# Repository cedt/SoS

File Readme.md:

# Science on a Stick 

---

### Folder Structure 
```
.
├── Arduino Code 				→ Contains code to be uploaded to Arduino 
│   └── SOS_Arduino_code
│       └── SOS_Arduino_code.ino
├── Arduino PCB and Hardware			→ Contains Schematic, BOM etc
│   ├── BOM-magnetic_switch_sos_v1-2022.pdf	→ Bill of Materials for Reed switch circuit
│   ├── BOM-ScienceonStick_V7-April2022.pdf	→ Bill of Materials for Main PCB
│   ├── Hardware_Acquisition_Sources.docx	→ Suggested sources to acquire components
│   ├── magnetic_switch_sos_v1-2022.sch 	→ Circuit for trigger switch
│   ├── photogate-sos-v2-2022.brd
│   ├── photogate-sos-v2-2022.sch
│   ├── ScienceOnStick_V7-April2022.brd
│   └── ScienceOnStick_V7-April2022.sch 	→ Circuit for main PCB
├── Images and Photographs
│   └── plots
│       └── ... plots created using experiments ... 
├── Python Code
│   ├── Analysis.ipynb
│   └── SoS_Acquisition.py
└── Structure
    ├── Structure Type 1
    │   ├── bar_inside.sbp
    │   ├── bar_outside.sbp
    │   ├── bars.crv
    │   ├── bars.png
    │   ├── base.crv
    │   ├── base_outside.sbp
    │   ├── base.png
    │   ├── flange.crv
    │   ├── flange_inner.sbp
    │   ├── flange_outside.sbp
    │   ├── flange.png
    │   ├── inside.sbp
    │   ├── via.crv
    │   ├── via_inside.sbp
    │   ├── via_outside.sbp
    │   └── via.png
    └── Structure Type 2
        ├── base.crv
        ├── base.png
        ├── correction.sbp
        ├── inside_baseandvia.sbp
        ├── outer_baseandvia.sbp
        ├── stand.crv
        ├── stand_in.sbp
        ├── stand_out.sbp
        ├── stand.png
        ├── via.crv
        ├── VIA-INNER.LOG
        ├── via-inner.sbp
        ├── VIA_OUTER.LOG
        ├── via_outer.sbp
        └── via.png
 ```

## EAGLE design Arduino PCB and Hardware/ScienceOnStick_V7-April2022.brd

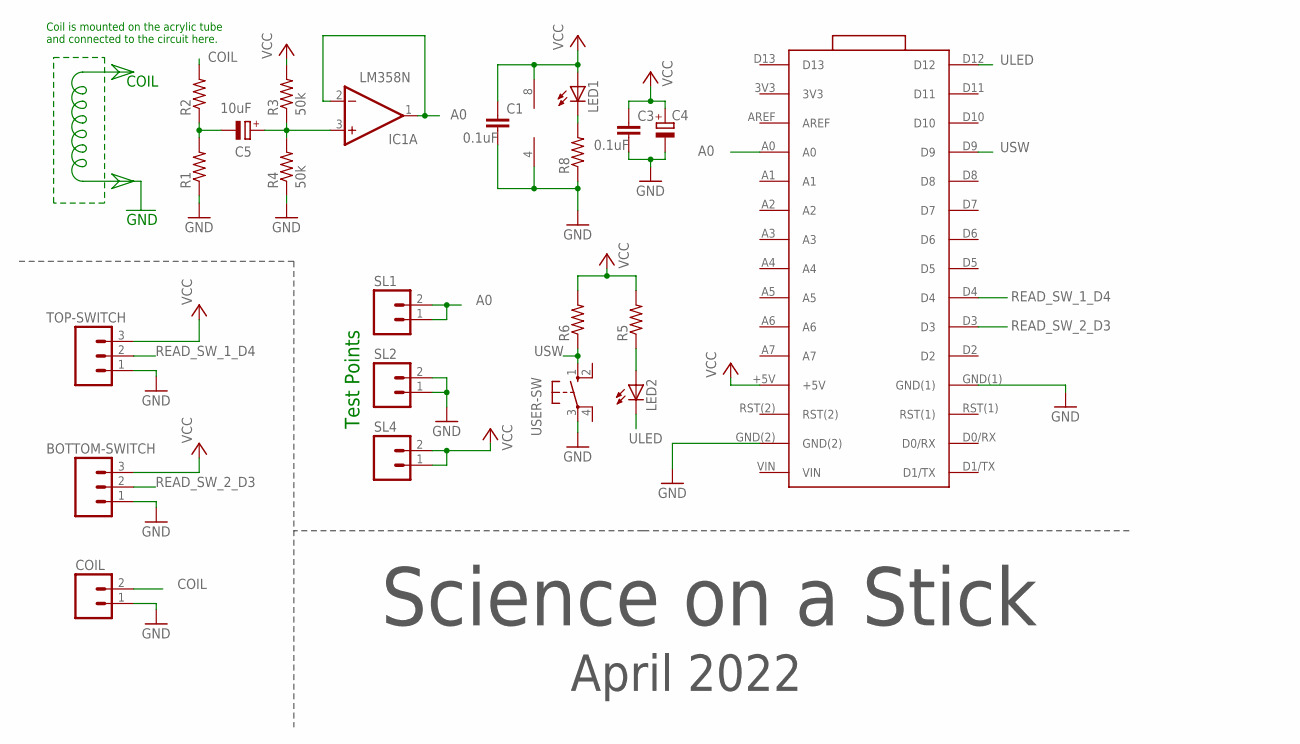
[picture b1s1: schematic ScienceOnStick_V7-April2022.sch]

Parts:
BOTTOM-SWITCH: M03; 03P
C1, C3: 0.1uF; C025-025X050
C4: CPOL-EUE2.5-6; E2,5-6
C5: 10uF; E2,5-6
COIL: M02; 02P
IC1: LM358N; DIL08
LED1, LED2: LED3MM
R1, R2, R5, R6, R8: RESISTOR0207/7; 0207/7
R3, R4: 50k; 0207/7
SL1, SL2, SL4: M02; 02P
TOP-SWITCH: M03; 03P
U$1: ARDUINO_NANO_3_ARDUINO(NANO_3.0); ARDUINO_NANO_3_ARDUINO_NANO_30PIN
USER-SW: 40-XX; B3F-40XX

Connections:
A0: IC1.1 (OUT), IC1.2 (-IN), SL1.1, SL1.2, U$1.A0
CLAMP_SIGNAL: C5.+, IC1.3 (+IN), R3.1, R4.2
COIL: COIL.2, R2.2
GND: BOTTOM-SWITCH.1, C1.2, C3.2, C4.-, COIL.1, IC1.4 (V-), R1.1, R4.1, R8.1, SL2.1, SL2.2, TOP-SWITCH.1, U$1.GND(1), U$1.GND(2), USER-SW.3
unnamed: C5.-, R1.2, R2.1
unnamed: LED2.A, R5.1
unnamed: LED1.K (C), R8.2
READ_SW_1_D4: TOP-SWITCH.2, U$1.D4
READ_SW_2_D3: BOTTOM-SWITCH.2, U$1.D3
ULED: LED2.K (C), U$1.D12
USW: R6.1, U$1.D9, USER-SW.1 (S)
VCC: BOTTOM-SWITCH.3, C1.1, C3.1, C4.+, IC1.8 (V+), LED1.A, R3.2, R5.2, R6.2, SL4.1, SL4.2, TOP-SWITCH.3, U$1.+5V

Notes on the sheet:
Science on a Stick
April 2022
Coil is mounted on the acrylic tube and connected to the circuit here.
COIL
GND
Test Points

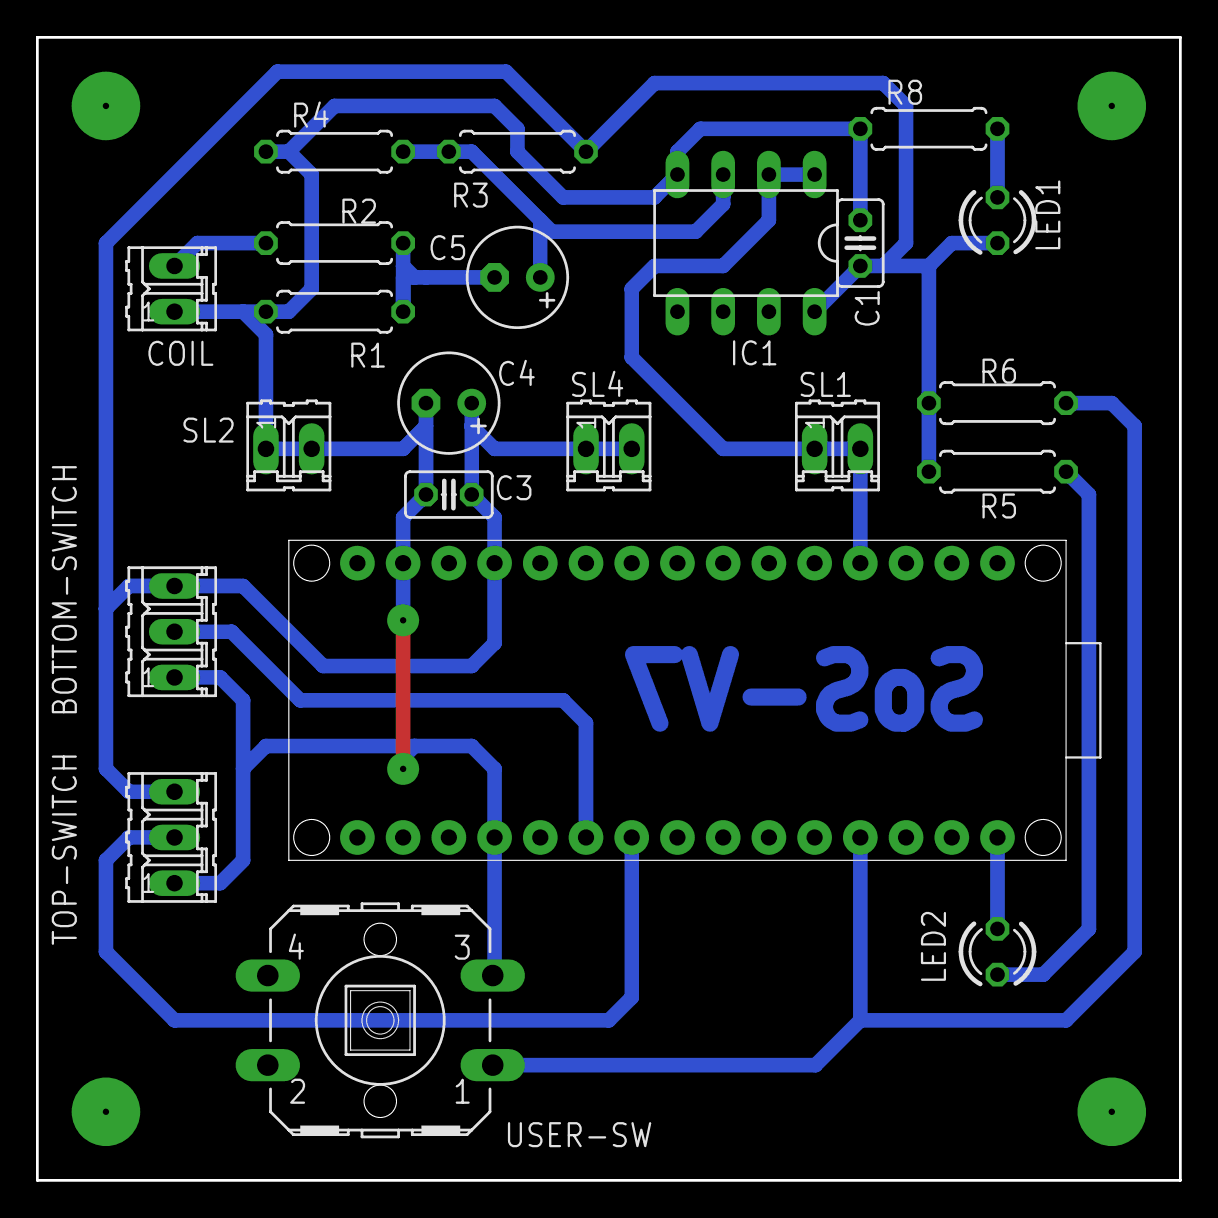
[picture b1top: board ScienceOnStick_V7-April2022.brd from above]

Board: 2 copper layers, 63.5 x 63.5 mm, 22 parts (0 on the bottom side), 12 nets.

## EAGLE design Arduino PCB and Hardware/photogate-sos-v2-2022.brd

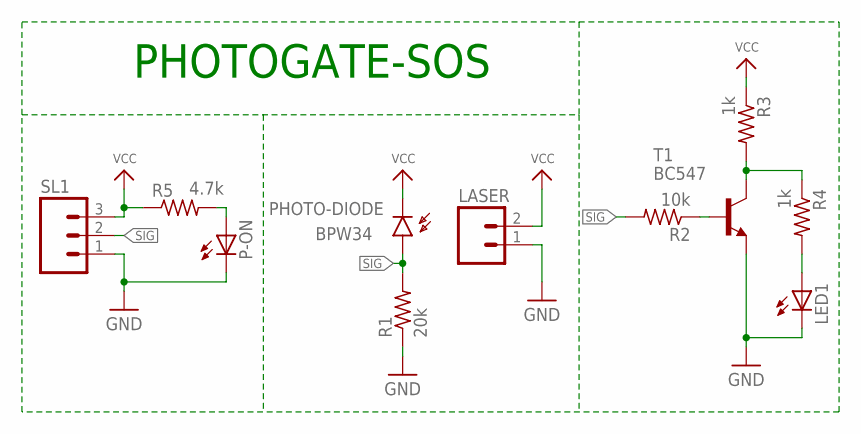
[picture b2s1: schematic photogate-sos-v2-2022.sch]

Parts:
LASER: M02; 02P
LED1: LED3MM
P-ON: LED3MM
PHOTO-DIODE: BPW34; BPW32
R1: 20k; 0204/7
R2: 10k; 0204/7
R3, R4: 1k; 0204/7
R5: 4.7k; 0204/7
SL1: M03; 03P
T1: BC547; TO92

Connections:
GND: LASER.1, LED1.K (C), P-ON.K (C), R1.1, SL1.1, T1.1 (E)
unnamed: R2.1, T1.2 (B)
unnamed: R3.2, R4.1, T1.3 (C)
unnamed: LED1.A, R4.2
unnamed: P-ON.A, R5.2
SIG: PHOTO-DIODE.A, R1.2, R2.2, SL1.2
VCC: LASER.2, PHOTO-DIODE.K (C), R3.1, R5.1, SL1.3

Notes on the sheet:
PHOTOGATE-SOS

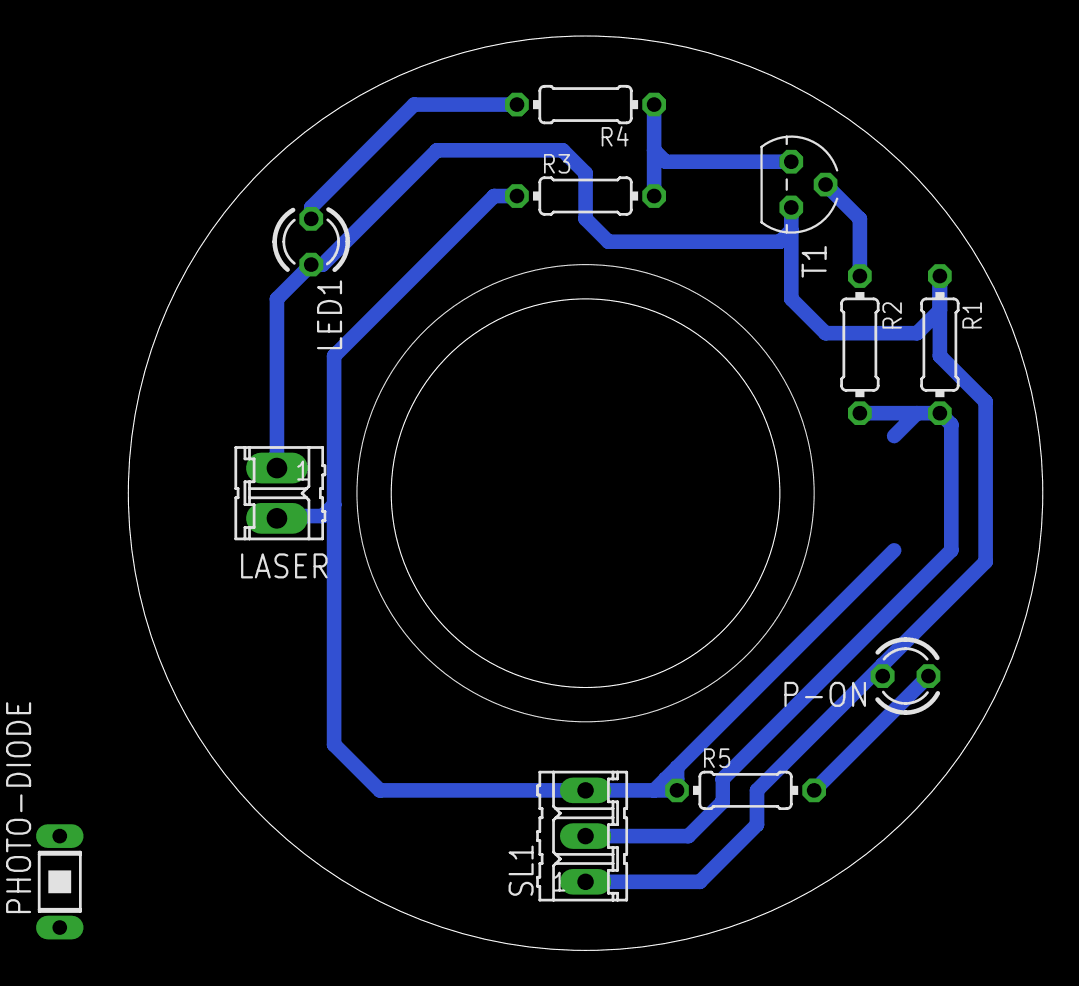
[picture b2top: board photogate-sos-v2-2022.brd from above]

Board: 2 copper layers, 50.8 x 50.8 mm, 11 parts (0 on the bottom side), 7 nets.

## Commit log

2022-10-28 All files added
2022-10-28 Readme modified
2022-10-28 data folder path changed
2024-07-06 change the value of plt.pause() from 0.001 to 0.1.
    The change is done so as the exp. is completed we observe graph on python eliminating the problem that all the graph will appear once the whole completion is done.
    DESCRIPTION FOR plt.pause()
    The command stop the execution of script for a given value of seconds this pause is require so that neccessary time is allowed for python to update the graph.
    link:- https://saturncloud.io/blog/how-to-pause-a-for-loop-and-wait-for-user-input-in-matplotlib/#:~:text=pause()%20Function-,The%20plt.,the%20plot%20to%20the%20user.
2024-07-06 An addition of code is done so that directories is created if they are not present.
    The change is done to facilitate the user as he would not have to create directory on his own he can just download and run the code.
2024-07-06 An update in code is proposed.
    This update can help the user who are using the SOS for first time with this change they do not need to create directory on their own.
    The code will ensure that necessary directories is created and if they exist then no need for creation.
